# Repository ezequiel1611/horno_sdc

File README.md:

# HornoESP32 1.0

En el marco de una beca de servicio del Laboratorio de Control de la UTN Facultad Regional Paraná se realizó una actualización de un horno usado con fines académicos de forma que ahora el mismo use una placa de desarrollo ESP32 DevKit V1 como microcontrolador dotando así al equipo de la capacidad de conexión a internet. El microcontrolador maneja la potencia del horno mediante el uso de un TRIAC con control de disparo por ángulo de fase y cuenta con un sensor DHT11 para monitorear la temperatura del horno. Mediante la implementación de una base de datos en tiempo real (RTDB por Real Time Database) a través de la plataforma de Google Firebase es que interactúan tanto el microcontrolador como la aplicación web desarrollada para el control y monitoreo del sistema. El microcontrolador realiza peticiones a la RTDB cada 5 segundos actualizando la información de la temperatura del horno y verificando si la potencia empleada es la seleccionada por el usuario, mientras que al mismo tiempo la aplicación web lee cada segundo de la RTDB la información de la temperatura y la muestra en un gráfico temporal además de proveerle al usuario de un control deslizable para seleccionar la potencia del horno en una escala del 0% al 100%.

# Control de Potencia

El control de disparo del TRIAC por ángulo de fase se basa en la conexión de la tensión de red con la carga en cualquier punto de la semionda de forma sincronizada, de forma que se puede "recortar" la tensión sinusoidal en sectores más pequeños regulando así la potencia aplicada a la carga.

En la siguiente imagen se puede ver que al entregar el 50% de la potencia a la carga el forma de onda sinusoidal se ve "recortada" a la mitad de cada semiciclo.

El circuito empleado para lograr este funcionamiento es el siguiente:

Para más información sobre el diseño y teoría de funcionamiento del circuito, puede leer la documentación provista: [Teoría y Diseño Dimmer](https://github.com/ezequiel1611/horno_sdc/blob/main/Dimmer/TP2_Potencia.pdf)

# Introducción a Firebase y sus Beneficios

Firebase es una plataforma desarrollada por Google que ofrece una amplia gama de servicios para el desarrollo de aplicaciones móviles y web. Uno de los servicios más destacados que ofrece Firebase es su **base de datos en tiempo real**, que proporciona una solución eficiente para almacenar y sincronizar datos en tiempo real entre usuarios y dispositivos.

## Beneficios de usar la base de datos en tiempo real de Firebase:

1. **Sincronización en tiempo real:**  
   Los cambios realizados en la base de datos se reflejan instantáneamente en todos los dispositivos conectados. Esto facilita la creación de aplicaciones colaborativas y en tiempo real donde los usuarios pueden ver actualizaciones al instante.

2. **Facilidad de integración:**  
   Firebase ofrece bibliotecas para una variedad de plataformas y frameworks, lo que simplifica la integración en aplicaciones móviles y web existentes.

3. **Seguridad y autenticación:**  
   Firebase proporciona reglas de seguridad personalizables y autenticación integrada con otros servicios de Google, lo que ayuda a proteger los datos del usuario y controlar el acceso a la base de datos.

4. **Escalabilidad y disponibilidad:**  
   Al ser una plataforma en la nube administrada por Google, Firebase ofrece una alta escalabilidad y disponibilidad, sin preocuparse por la gestión de la infraestructura subyacente.

Firebase provee una facilidad a la hora de programar el microcontrolador ESP32 ya que con conectar el mismo a internet ya es posible interactuar con la base de datos de forma rápida e intuitiva debido a las librerías provistas para su uso. Por otro lado, también permite el alojamiento de una aplicación web permitiendo así el uso de un dominio en internet para crear una página web que sirva para control y monitoreo del sistema.

# Aplicación Web

Usando la herramienta de desarrollo online Replit se diseño la página web para monitorear y controlar el HornoESP32. Este desarrollo fue llevado a cabo en HTML y sus archivos HTML, CSS y JS puede accederse a través de: [Replit-HornoESP32](https://replit.com/@lautaroezequie3/HornoSDC)

## Monitoreo de la Temperatura

Al ingresar a la página usted verá un gráfico vacío, cuando haga click en el boton "On/Off" se habilitará la toma de datos y verá como cada segundo se imprime en la gráfica la temperatura del horno. Usted puede observar en tiempo real como varía la temperatura del horno mediante esta gráfica donde se indica en el eje X hora, minutos y segundos del dato tomado y en el eje Y la temperatura del horno en grados Celsius. Si quiere saber el valor exacto de un dato solo debe posar el mouse sobre el punto de la gráfica deseado, usted puede pausar la actualización de la gráfica haciendo click nuevamente en el botón "On/Off" si así lo desea.

Además de la visualización en tiempo real, la página web tiene un botón "Datos" el cual al presionarlo realiza la descarga de un archivo "datos.m" que contiene en cada renglón el dato de temperatura de cada punto de la gráfica. Esto con la finalidad de poder realizar un posterior análisis empleando GNU Octave o MatLab como se ve a continuación.

## Control de la Temperatura

Una vez en la página web usted podrá ver controlador deslizable que indica la potencia del horno en una escala del 0% al 100%, este controlador tiene un paso de 10% por lo que usted podrá determinar la potencia del horno a voluntad mediante la variación de este controlador deslizable. Este control deslizable envia el dato de a que ángulo se debe realizar el disparo del TRIAC a la base de datos y es el ESP32 el cual luego lee esta información y ajusta el ángulo de disparo al deseado para aśi establecer la potencia del horno a la requerida por el usuario.

**[Aplicación Web](https://horno-sdc.web.app/)**

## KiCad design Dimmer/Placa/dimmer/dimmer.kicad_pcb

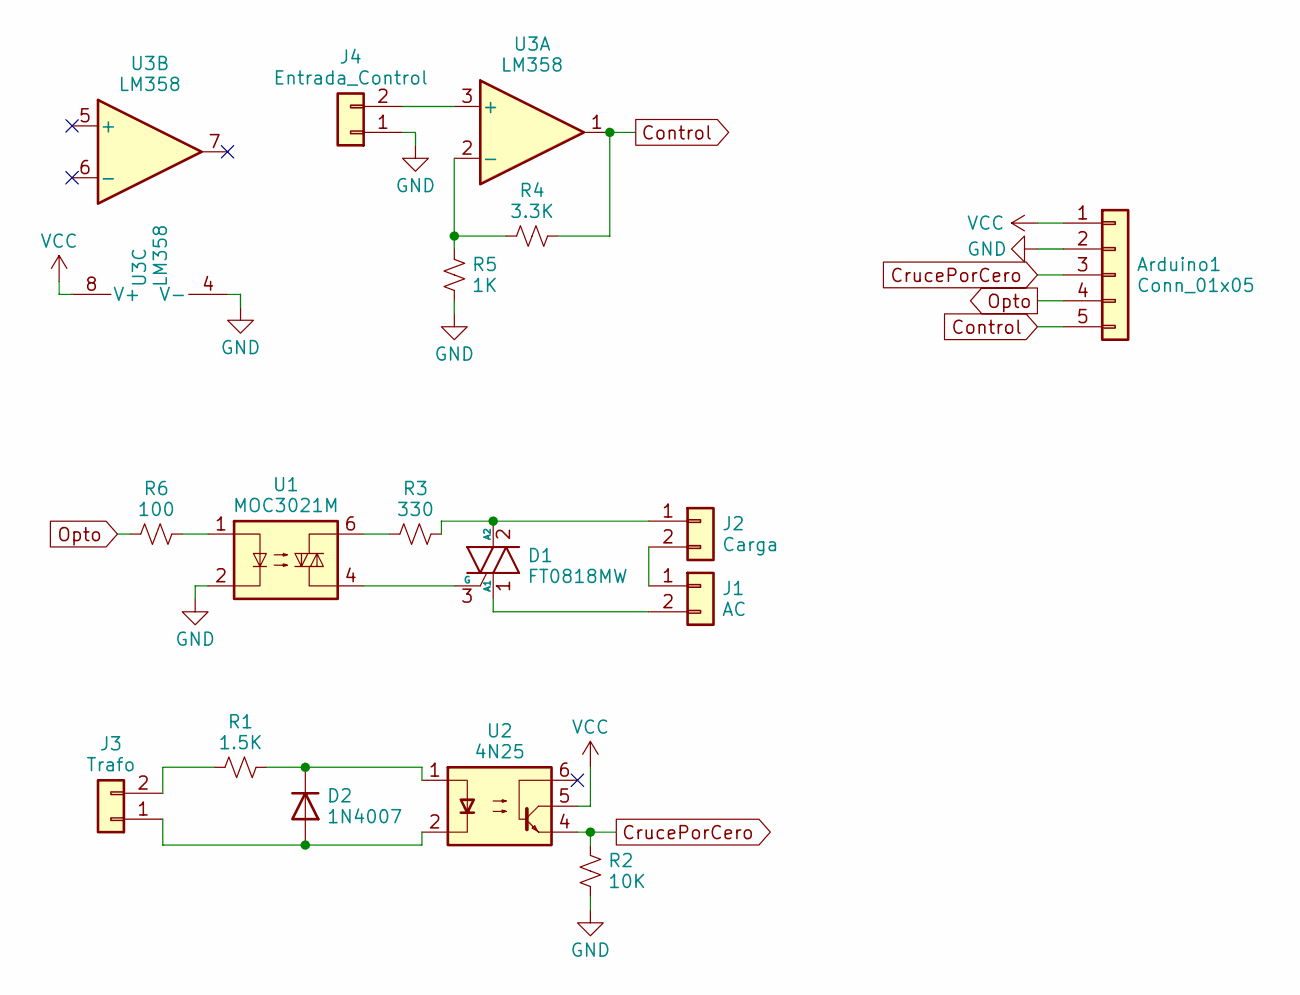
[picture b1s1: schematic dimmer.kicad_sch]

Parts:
Arduino1: Conn_01x05; PinSocket_1x05_P2.54mm_Vertical
D1: FT0818MW; TO-220-3_Vertical
D2: 1N4007; D_DO-41_SOD81_P10.16mm_Horizontal
J1: AC; TerminalBlock_bornier-2_P5.08mm
J2: Carga; TerminalBlock_bornier-2_P5.08mm
J3: Trafo; TerminalBlock_bornier-2_P5.08mm
J4: Entrada_Control; TerminalBlock_bornier-2_P5.08mm
R1: 1.5K; R_Axial_DIN0207_L6.3mm_D2.5mm_P10.16mm_Horizontal
R2: 10K; R_Axial_DIN0207_L6.3mm_D2.5mm_P10.16mm_Horizontal
R3: 330; R_Axial_DIN0207_L6.3mm_D2.5mm_P10.16mm_Horizontal
R4: 3.3K; R_Axial_DIN0207_L6.3mm_D2.5mm_P10.16mm_Horizontal
R5: 1K; R_Axial_DIN0207_L6.3mm_D2.5mm_P10.16mm_Horizontal
R6: 100; R_Axial_DIN0207_L6.3mm_D2.5mm_P10.16mm_Horizontal
U1: MOC3021M; DIP-6_W7.62mm_LongPads
U2: 4N25; DIP-6_W7.62mm_LongPads
U3: LM358; DIP-8_W7.62mm_LongPads

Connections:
Control: Arduino1.5, R4.2, U3.1
CrucePorCero: Arduino1.3, R2.1, U2.4
GND: Arduino1.2, J4.1, R2.2, R5.2, U1.2, U3.4 (V-)
unnamed: D1.1 (A1), J1.2
unnamed: D1.2 (A2), J2.1, R3.2
unnamed: D1.3 (G), U1.4
unnamed: D2.2 (A), J3.1, U2.2
unnamed: D2.1 (K), R1.2, U2.1
unnamed: J1.1, J2.2
unnamed: J3.2, R1.1
unnamed: J4.2, U3.3 (+)
unnamed: R3.1, U1.6
unnamed: R6.2, U1.1
unnamed: R4.1, R5.1, U3.2 (-)
Opto: Arduino1.4, R6.1
VCC: Arduino1.1, U2.5, U3.8 (V+)

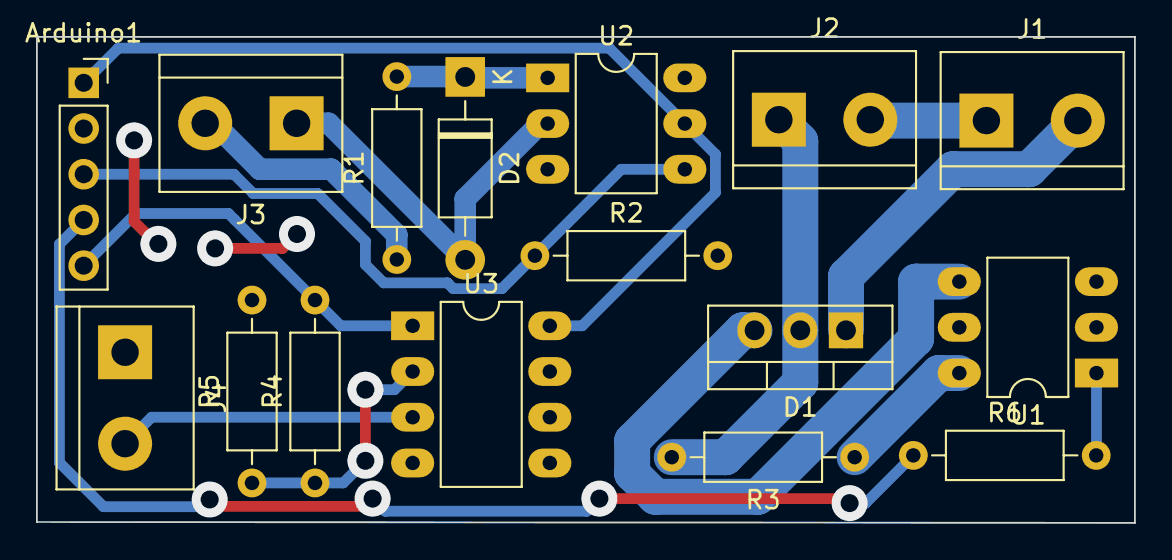
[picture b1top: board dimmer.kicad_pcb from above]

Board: 2 copper layers, 61.0 x 27.0 mm, 16 parts (0 on the bottom side), 16 nets.

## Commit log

2024-08-26 Archivos del módulo dimmer y código viejo del horno.
    Se añadieron los archivos de KiCad del módulo dimmer a usar, así como también el código empleado para su control, la teoría de diseño y funcionamiento y también los datasheets de los componentes empl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
2024-08-28 Primera versión del código
    Control de la potencia del foco usando un potenciómetro sin sensores de temperatura.
2024-09-25 HornoESP32 1.0
    Código para controlar el horno mediante ESP32 y comunicación con base de datos en tiempo real de Firebase.
2024-09-25 HornoESP32 1.0
    Ocultación de datos de api.
2024-09-25 App Web para el HornoESP32 1.0
    App Web para controlar y monitorear el HornoESP32 1.0
2024-09-25 Multimedia
    Imágenes añadidas para el README
2024-09-25 Preview web app
2024-09-26 Resultados primera prueba
2024-09-26 Test de analisis de datos
    Primera prueba de exportación de datos de la RTDB y su uso en el entorno de GNU Octave
2024-10-10 Adaptación para usar DHT11 o BMP180 a elección
2024-10-10 Integración de la librería Adafruit para BMP180
2025-02-06 Actualización de Seguridad
    Ahora el ESP32 debe autenticarse en el servidor para poder escribir en la base de datos.
2025-02-06 Cambios de Seguridad para la AppWeb
    Ahora la página web solicita un correo y contraseña para poder interactuar con el horno y visualizar los datos.
2025-02-06 Cambios de Seguridad
    Se eliminaron las claves de autenticación para mayor seguridad.
